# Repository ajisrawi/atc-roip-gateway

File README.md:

# ATC RoIP Gateway (VHF + HF, airborne)

Radio-over-IP gateway for aircraft ATC radios: bridges a VHF COM and an HF
transceiver to an IP network (Starlink aviation terminal) with an ED-137-style
RTP audio + PTT/COR stream.

```
Pilot/remote op ⇄ RTP over IP (Starlink) ⇄ [this gateway] ⇄ VHF COM + HF transceivers
```

## Deliverables

| Item | Where | Status |
|---|---|---|
| **Design document (PDF)** | `ATC-RoIP-Gateway-Design-Document.pdf` | 16 pages: study, diagrams, PCB, BOM, verification + schematic appendix |
| **Market study** | `docs/01-market-study.md` | sourced |
| **Design spec** | `docs/02-design-spec.md` | rev A |
| **Schematics** | `hardware/atc-roip-gateway/*.kicad_sch` | ERC 0 errors / 0 warnings, wired stubs + net labels |
| **PCB (4-layer, 125×95 mm)** | `hardware/atc-roip-gateway/atc-roip-gateway.kicad_pcb` | fully routed, 0 unconnected, 0 electrical DRC |
| **Fab outputs** | `hardware/atc-roip-gateway/fab/` | Gerber ZIP, drill, pick-and-place |
| **BOM** | `docs/BOM.csv` | 40 line items, 100 parts, MPNs assigned |
| **Firmware** | `firmware/` | ED-137-style stack (SIP + RTP/PTT/SQU + G.711), CMake, flash script |
| **Generators** | `tools/` | schematic/PCB/BOM/doc generation + checks (reproducible) |

## Hardware summary
| Block | Part |
|---|---|
| MCU | STM32H743VIT6 (Ethernet MAC + SAI, runs lwIP + RTP) |
| Ethernet | LAN8742A RMII PHY + magnetics-integrated RJ45 |
| Audio | TLV320AIC23B stereo codec — Left = VHF, Right = HF |
| Radio isolation | 600:600 Ω transformers (RX/TX ×2), PC817 optos (PTT + COR ×2) |
| Radio connector | DB25 (pinout in design spec §5.1) |
| Power | 28 V DC bus → LM2576HV-5.0 buck → AMS1117-3.3, split analog rail |

## Regenerating everything
```bash
python tools/design.py            # schematics
python tools/make_bom.py          # BOM from netlist
python tools/make_design_doc.py   # design document PDF
# PCB: tools/make_pcb.py (placement) + Freerouting + tools/power_fanout_final.py
```

## Status / caveats
- Rev A prototype: not TSO'd, no DO-160 qualification, no DO-178C artifacts.
- ED-137: hardware + firmware structured for the ED-137B Radio profile; exact
  extension bit-fields and SDP attributes must be verified against the
  licensed EUROCAE text + a conformance tool before claiming compliance.
- Transformer footprint (DIP-4) and DB25 gender are placeholders — confirm
  against the chosen audio transformer and aircraft harness.
- Firmware builds against STM32CubeH7 (user fetches; see `firmware/README.md`)
  and needs the four board-config files copied per `firmware/src/config/README.md`.

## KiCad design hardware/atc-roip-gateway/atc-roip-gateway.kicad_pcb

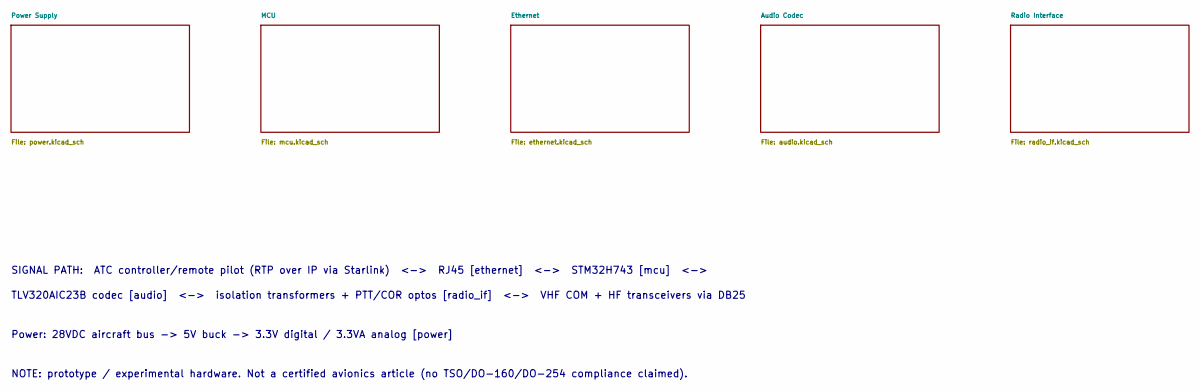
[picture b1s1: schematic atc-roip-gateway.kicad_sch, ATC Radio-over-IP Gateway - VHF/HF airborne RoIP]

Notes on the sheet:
SIGNAL PATH: ATC controller/remote pilot (RTP over IP via Starlink) <-> RJ45 [ethernet] <-> STM32H743 [mcu] <->
TLV320AIC23B codec [audio] <-> isolation transformers + PTT/COR optos [radio_if] <-> VHF COM + HF transceivers via DB25
Power: 28VDC aircraft bus -> 5V buck -> 3.3V digital / 3.3VA analog [power]
NOTE: prototype / experimental hardware. Not a certified avionics article (no TSO/DO-160/DO-254 compliance claimed).

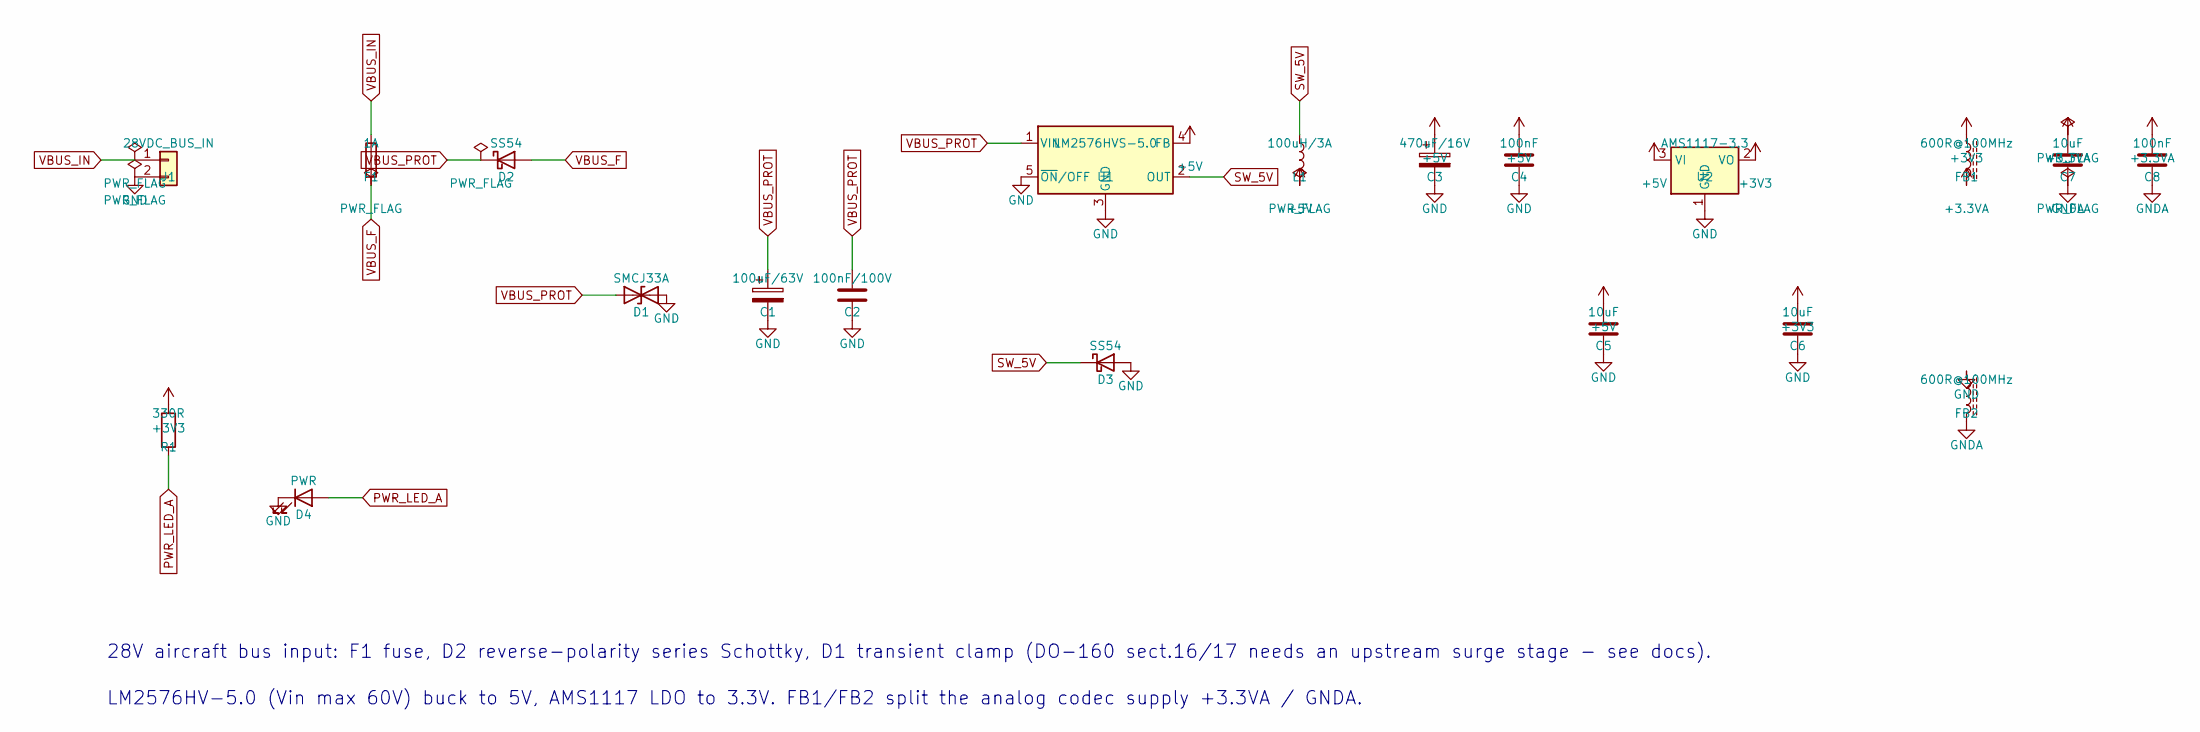
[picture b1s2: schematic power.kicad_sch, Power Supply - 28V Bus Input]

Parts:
C1: 100uF/63V; CP_Elec_8x10
C2: 100nF/100V; C_0805_2012Metric
C3: 470uF/16V; CP_Elec_8x10
C4, C8: 100nF; C_0603_1608Metric
C5, C6, C7: 10uF; C_0805_2012Metric
D1: SMCJ33A; D_SMC
D2, D3: SS54; D_SMA
D4: PWR; LED_0603_1608Metric
F1: 1A; Fuse_1206_3216Metric
FB1, FB2: 600R@100MHz; L_0805_2012Metric
J1: 28VDC_BUS_IN; TerminalBlock_Phoenix_MKDS-1,5-2_1x02_P5.00mm_Horizontal
L1: 100uH/3A; L_12x12mm_H8mm
R1: 330R; R_0603_1608Metric
U1: LM2576HVS-5.0; TO-263-5_TabPin3
U2: AMS1117-3.3; SOT-223-3_TabPin2

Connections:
+3V3: C6.1, FB1.1, R1.1, U2.2 (VO); also elsewhere on the board
PWR_LED_A: D4.2 (A), R1.2
SW_5V: D3.1 (K), L1.1, U1.2 (OUT)

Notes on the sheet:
28V aircraft bus input: F1 fuse, D2 reverse-polarity series Schottky, D1 transient clamp (DO-160 sect.16/17 needs an upstream surge stage - see docs).
LM2576HV-5.0 (Vin max 60V) buck to 5V, AMS1117 LDO to 3.3V. FB1/FB2 split the analog codec supply +3.3VA / GNDA.

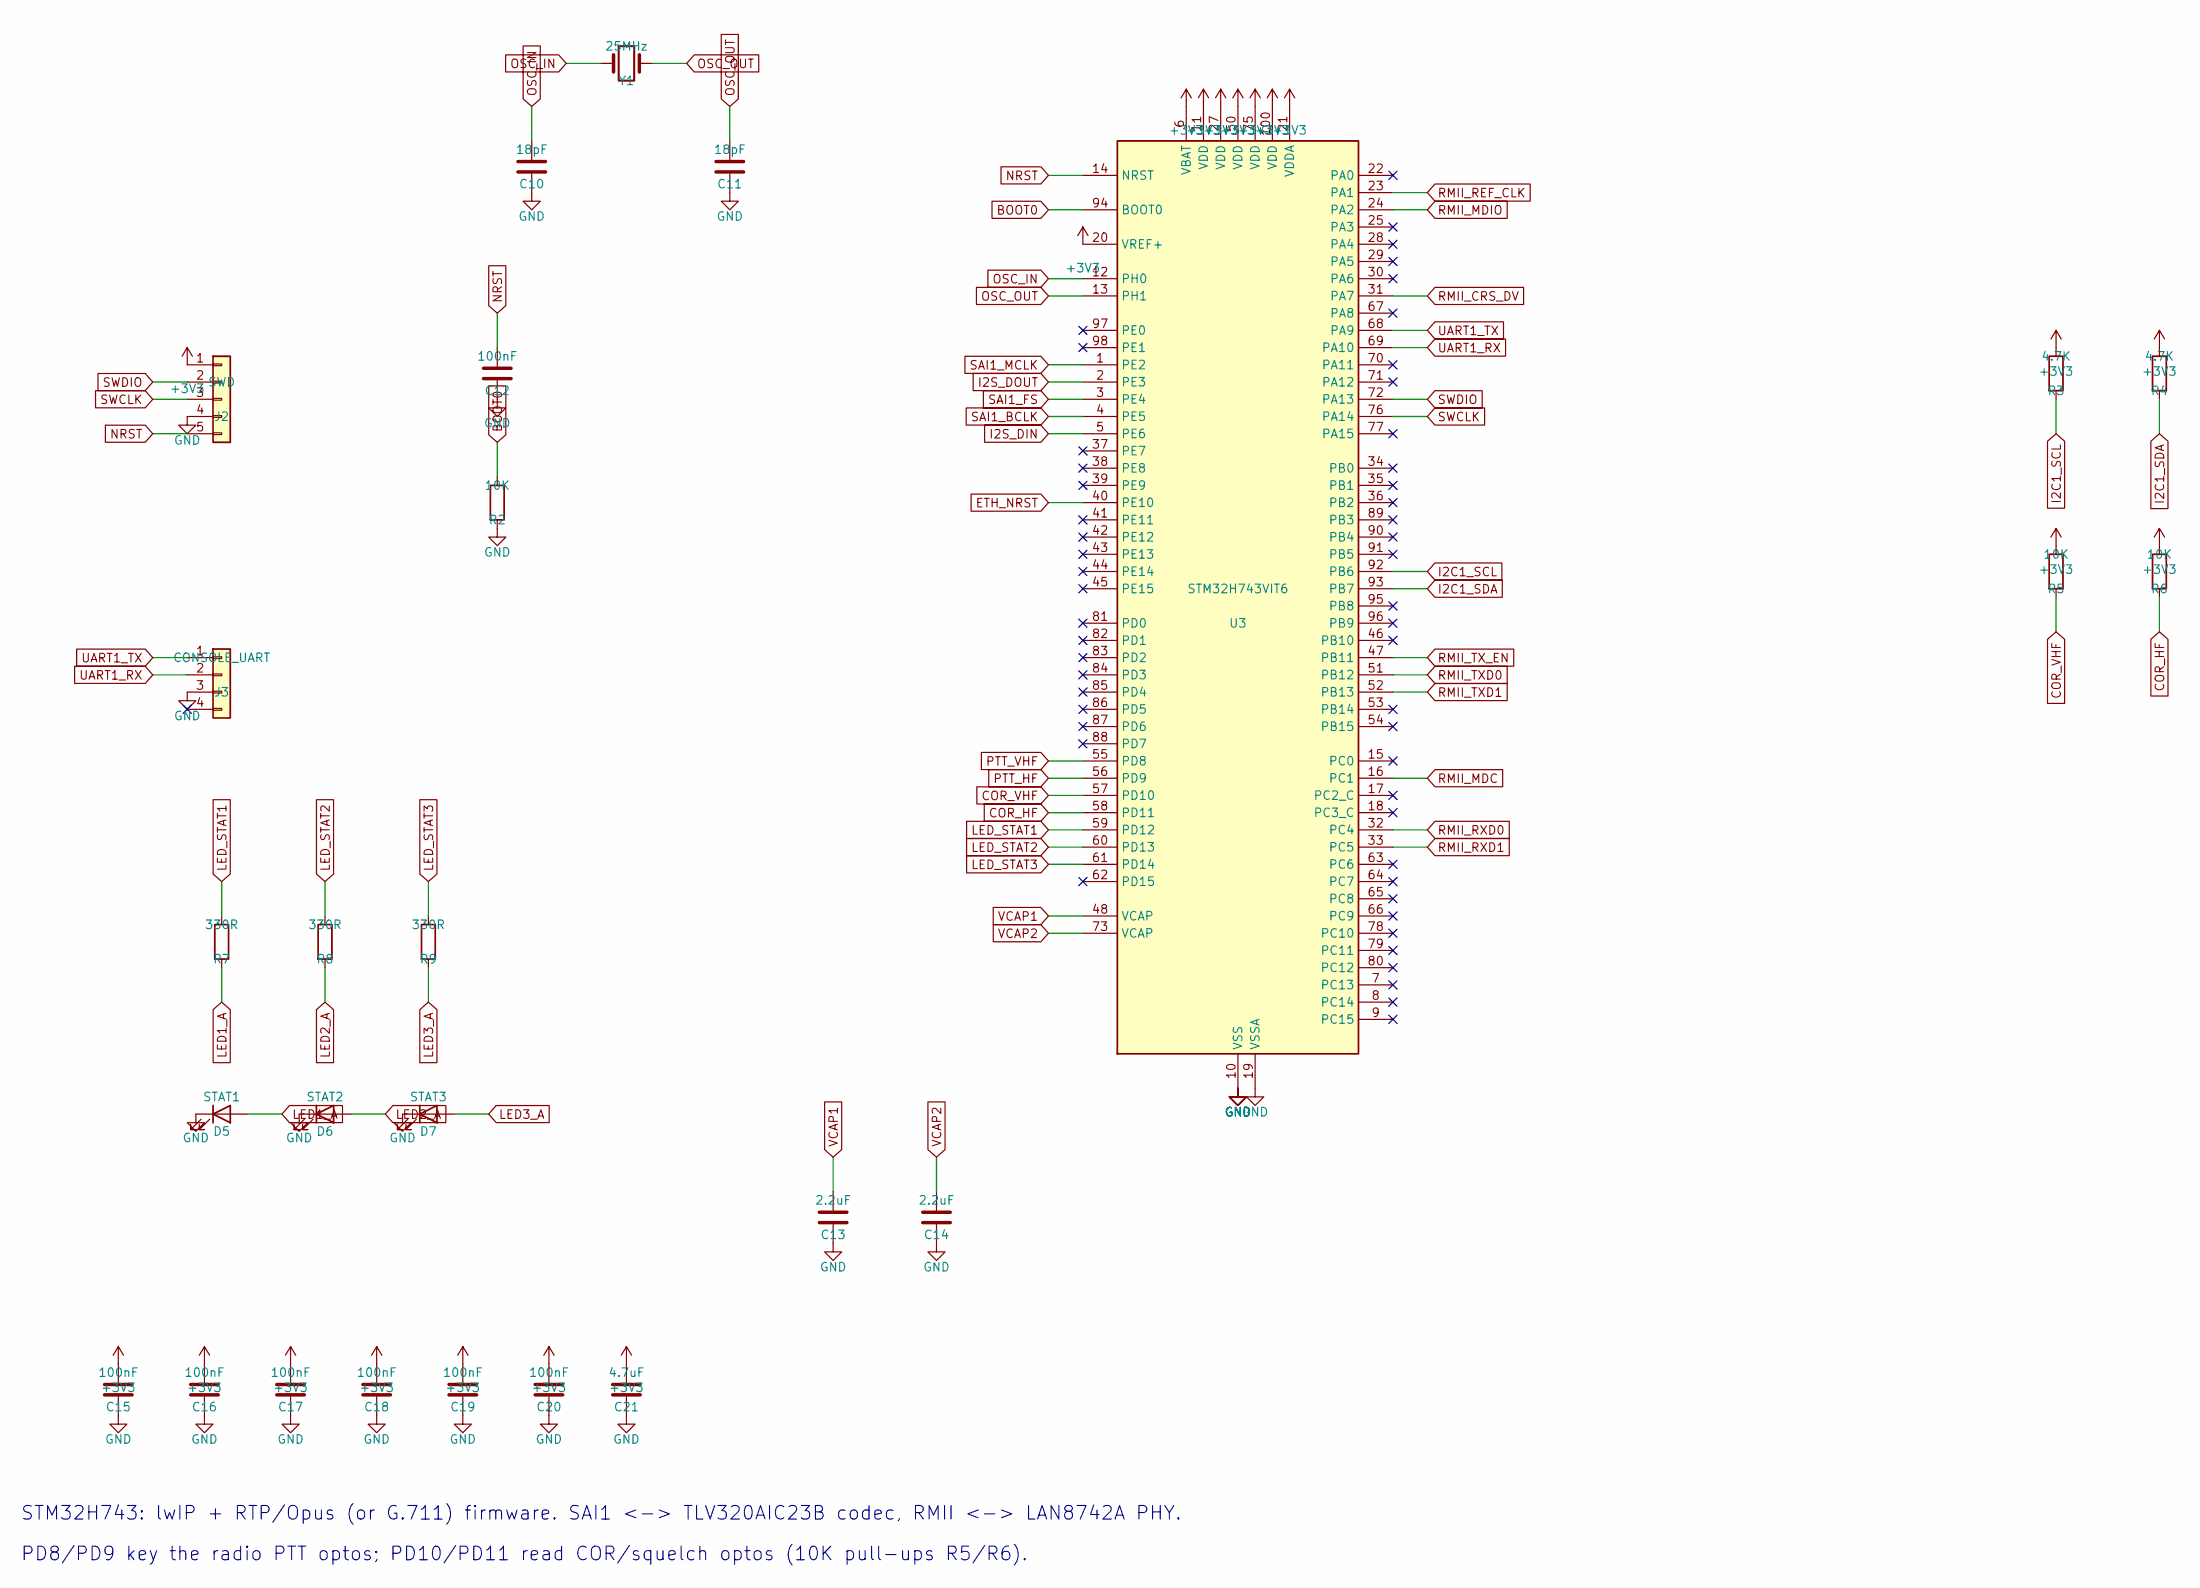
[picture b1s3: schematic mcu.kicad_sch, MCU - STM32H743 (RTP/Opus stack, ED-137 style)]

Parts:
C10, C11: 18pF; C_0603_1608Metric
C12, C15, C16, C17, C18, C19, C20: 100nF; C_0603_1608Metric
C13, C14: 2.2uF; C_0805_2012Metric
C21: 4.7uF; C_0805_2012Metric
D5: STAT1; LED_0603_1608Metric
D6: STAT2; LED_0603_1608Metric
D7: STAT3; LED_0603_1608Metric
J2: SWD; PinHeader_1x05_P2.54mm_Vertical
J3: CONSOLE_UART; PinHeader_1x04_P2.54mm_Vertical
R2, R5, R6: 10K; R_0603_1608Metric
R3, R4: 4.7K; R_0603_1608Metric
R7, R8, R9: 330R; R_0603_1608Metric
U3: STM32H743VIT6; LQFP-100_14x14mm_P0.5mm
Y1: 25MHz; Crystal_SMD_3225-4Pin_3.2x2.5mm

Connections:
+3V3: C15.1, C16.1, C17.1, C18.1, C19.1, C20.1, C21.1, J2.1, R3.1, R4.1, R5.1, R6.1, U3.6 (VBAT), U3.11 (VDD), U3.20 (VREF+), U3.21 (VDDA), U3.27 (VDD), U3.50 (VDD), U3.75 (VDD), U3.100 (VDD); also elsewhere on the board
BOOT0: R2.1, U3.94 (BOOT0)
COR_HF: R6.2, U3.58 (PD11); also elsewhere on the board
COR_VHF: R5.2, U3.57 (PD10); also elsewhere on the board
ETH_NRST: U3.40 (PE10); also elsewhere on the board
I2C1_SCL: R3.2, U3.92 (PB6); also elsewhere on the board
I2C1_SDA: R4.2, U3.93 (PB7); also elsewhere on the board
I2S_DIN: U3.5 (PE6); also elsewhere on the board
I2S_DOUT: U3.2 (PE3); also elsewhere on the board
LED1_A: D5.2 (A), R7.2
LED2_A: D6.2 (A), R8.2
LED3_A: D7.2 (A), R9.2
LED_STAT1: R7.1, U3.59 (PD12)
LED_STAT2: R8.1, U3.60 (PD13)
LED_STAT3: R9.1, U3.61 (PD14)
NRST: C12.1, J2.5, U3.14 (NRST)
OSC_IN: C10.1, U3.12 (PH0), Y1.1
OSC_OUT: C11.1, U3.13 (PH1), Y1.2
PTT_HF: U3.56 (PD9); also elsewhere on the board
PTT_VHF: U3.55 (PD8); also elsewhere on the board
RMII_CRS_DV: U3.31 (PA7); also elsewhere on the board
RMII_MDC: U3.16 (PC1); also elsewhere on the board
RMII_MDIO: U3.24 (PA2); also elsewhere on the board
RMII_REF_CLK: U3.23 (PA1); also elsewhere on the board
RMII_RXD0: U3.32 (PC4); also elsewhere on the board
RMII_RXD1: U3.33 (PC5); also elsewhere on the board
RMII_TXD0: U3.51 (PB12); also elsewhere on the board
RMII_TXD1: U3.52 (PB13); also elsewhere on the board
RMII_TX_EN: U3.47 (PB11); also elsewhere on the board
SAI1_BCLK: U3.4 (PE5); also elsewhere on the board
SAI1_FS: U3.3 (PE4); also elsewhere on the board
SAI1_MCLK: U3.1 (PE2); also elsewhere on the board
SWCLK: J2.3, U3.76 (PA14)
SWDIO: J2.2, U3.72 (PA13)
UART1_RX: J3.2, U3.69 (PA10)
UART1_TX: J3.1, U3.68 (PA9)
VCAP1: C13.1, U3.48 (VCAP)
VCAP2: C14.1, U3.73 (VCAP)

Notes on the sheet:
STM32H743: lwIP + RTP/Opus (or G.711) firmware. SAI1 <-> TLV320AIC23B codec, RMII <-> LAN8742A PHY.
PD8/PD9 key the radio PTT optos; PD10/PD11 read COR/squelch optos (10K pull-ups R5/R6).

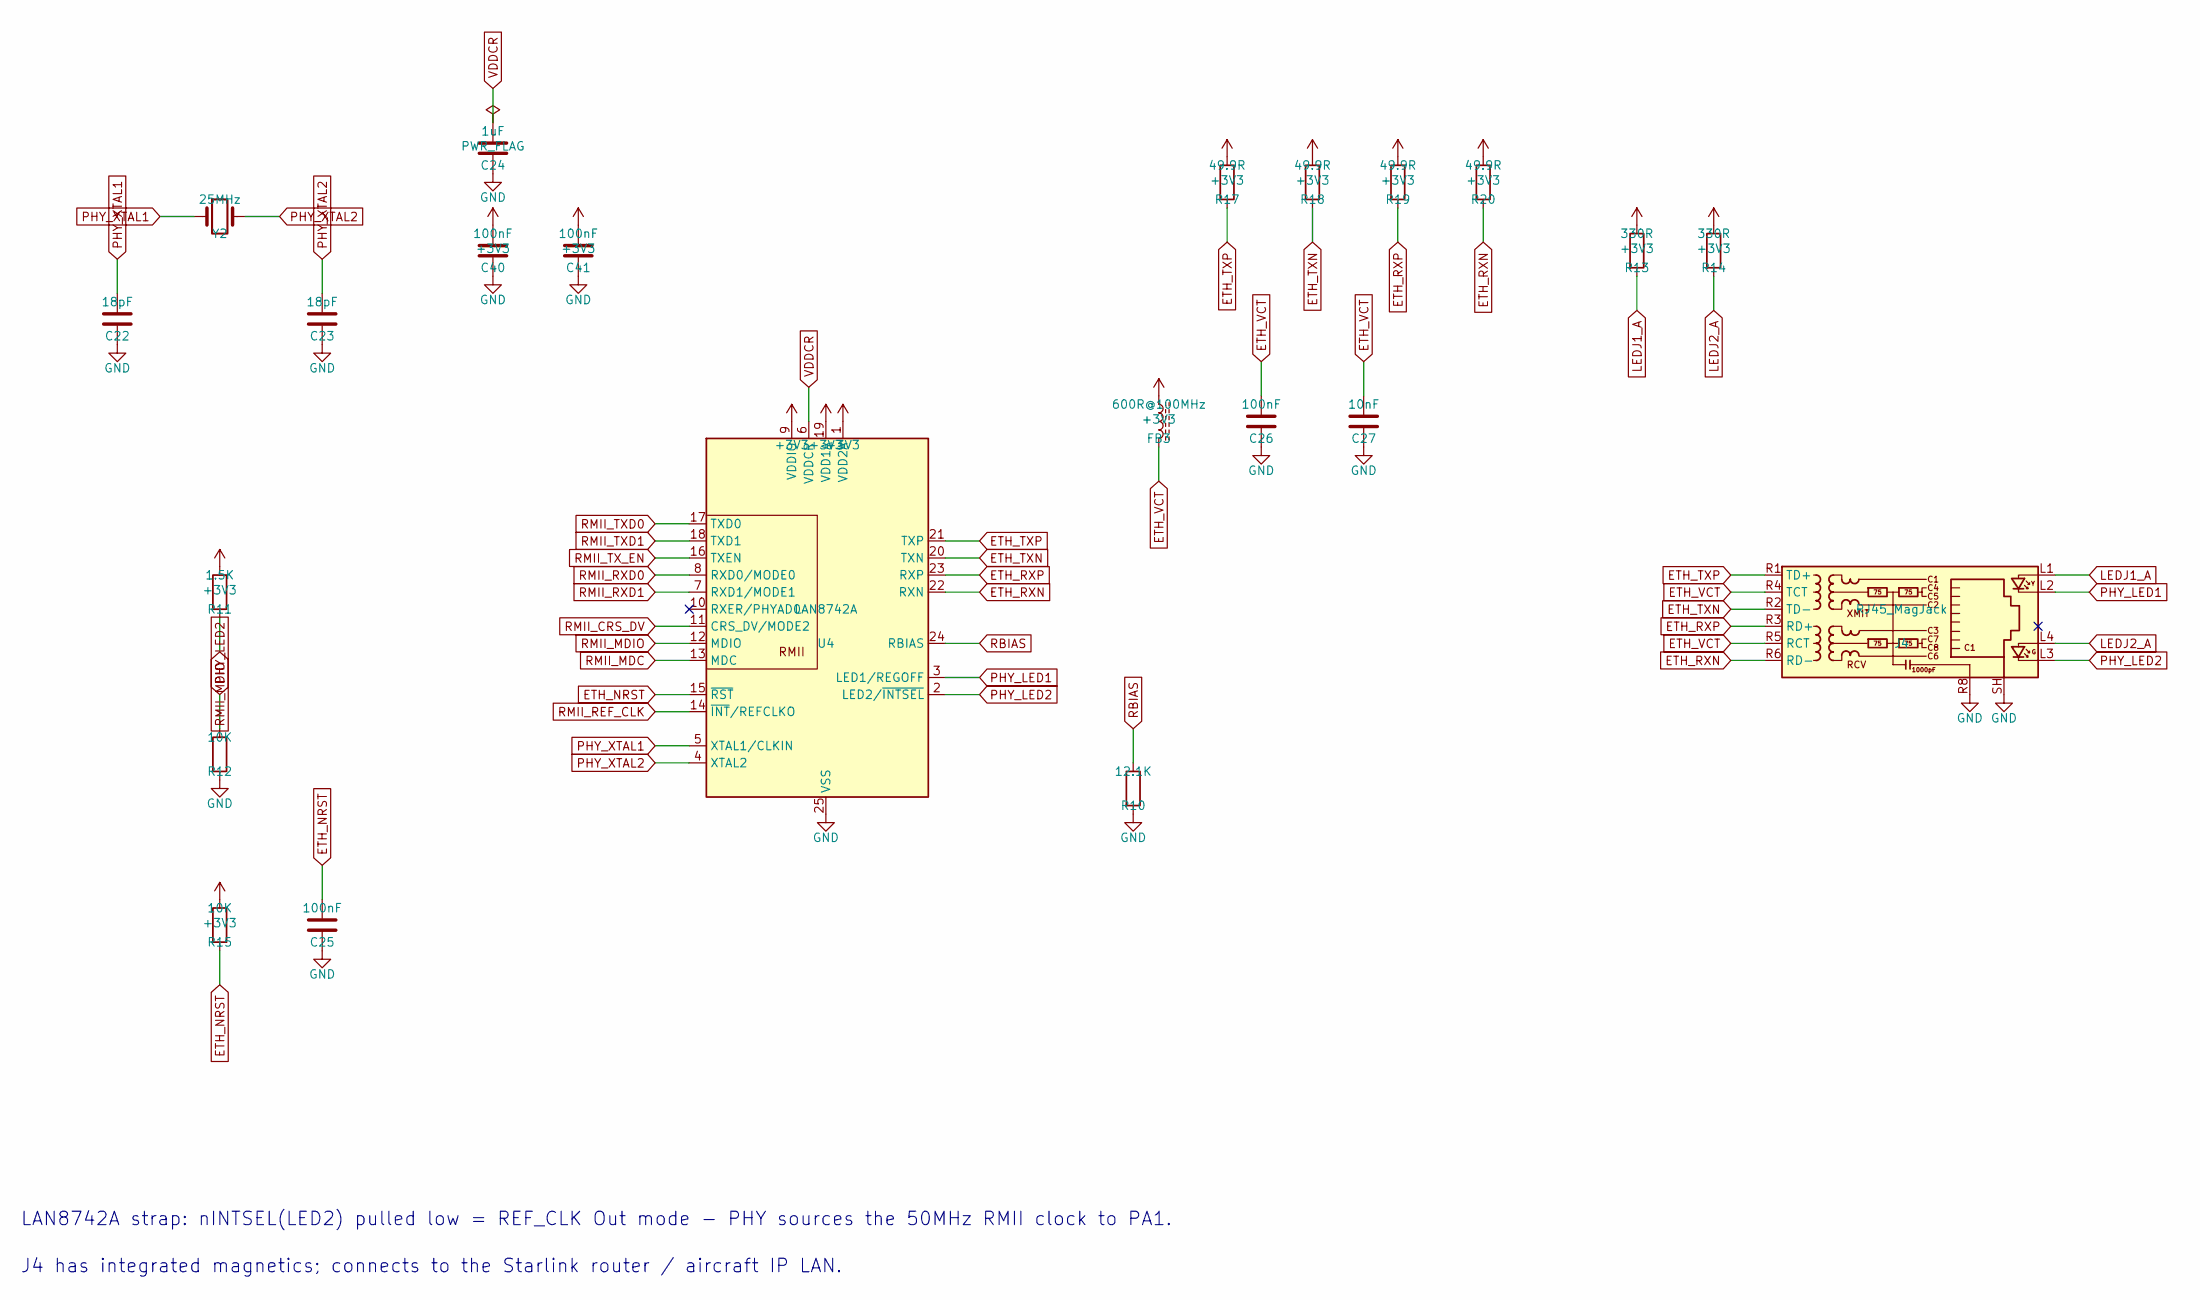
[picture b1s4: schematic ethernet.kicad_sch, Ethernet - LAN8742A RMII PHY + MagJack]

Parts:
C22, C23: 18pF; C_0603_1608Metric
C24: 1uF; C_0603_1608Metric
C25, C26, C40, C41: 100nF; C_0603_1608Metric
C27: 10nF; C_0603_1608Metric
FB3: 600R@100MHz; L_0805_2012Metric
J4: RJ45_MagJack; RJ45_Amphenol_RJMG1BD3B8K1ANR
R10: 12.1K; R_0603_1608Metric
R11: 1.5K; R_0603_1608Metric
R12, R15: 10K; R_0603_1608Metric
R13, R14: 330R; R_0603_1608Metric
R17, R18, R19, R20: 49.9R; R_0603_1608Metric
U4: LAN8742A; QFN-24-1EP_4x4mm_P0.5mm_EP2.6x2.6mm
Y2: 25MHz; Crystal_SMD_3225-4Pin_3.2x2.5mm

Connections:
+3V3: C40.1, C41.1, FB3.1, R11.1, R13.1, R14.1, R15.1, R17.1, R18.1, R19.1, R20.1, U4.1 (VDD2A), U4.9 (VDDIO), U4.19 (VDD1A); also elsewhere on the board
ETH_NRST: C25.1, R15.2, U4.15 (~RST); also elsewhere on the board
ETH_RXN: J4.R6 (RD-), R20.2, U4.22 (RXN)
ETH_RXP: J4.R3 (RD+), R19.2, U4.23 (RXP)
ETH_TXN: J4.R2 (TD-), R18.2, U4.20 (TXN)
ETH_TXP: J4.R1 (TD+), R17.2, U4.21 (TXP)
ETH_VCT: C26.1, C27.1, FB3.2, J4.R4 (TCT), J4.R5 (RCT)
LEDJ1_A: J4.L1, R13.2
LEDJ2_A: J4.L4, R14.2
PHY_LED1: J4.L2, U4.3 (LED1/REGOFF)
PHY_LED2: J4.L3, R12.1, U4.2 (LED2/~INTSEL)
PHY_XTAL1: C22.1, U4.5 (XTAL1/CLKIN), Y2.1
PHY_XTAL2: C23.1, U4.4 (XTAL2), Y2.2
RBIAS: R10.1, U4.24 (RBIAS)
RMII_CRS_DV: U4.11 (CRS_DV/MODE2); also elsewhere on the board
RMII_MDC: U4.13 (MDC); also elsewhere on the board
RMII_MDIO: R11.2, U4.12 (MDIO); also elsewhere on the board
RMII_REF_CLK: U4.14 (~INT/REFCLKO); also elsewhere on the board
RMII_RXD0: U4.8 (RXD0/MODE0); also elsewhere on the board
RMII_RXD1: U4.7 (RXD1/MODE1); also elsewhere on the board
RMII_TXD0: U4.17 (TXD0); also elsewhere on the board
RMII_TXD1: U4.18 (TXD1); also elsewhere on the board
RMII_TX_EN: U4.16 (TXEN); also elsewhere on the board
VDDCR: C24.1, U4.6 (VDDCR)

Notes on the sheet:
LAN8742A strap: nINTSEL(LED2) pulled low = REF_CLK Out mode - PHY sources the 50MHz RMII clock to PA1.
J4 has integrated magnetics; connects to the Starlink router / aircraft IP LAN.

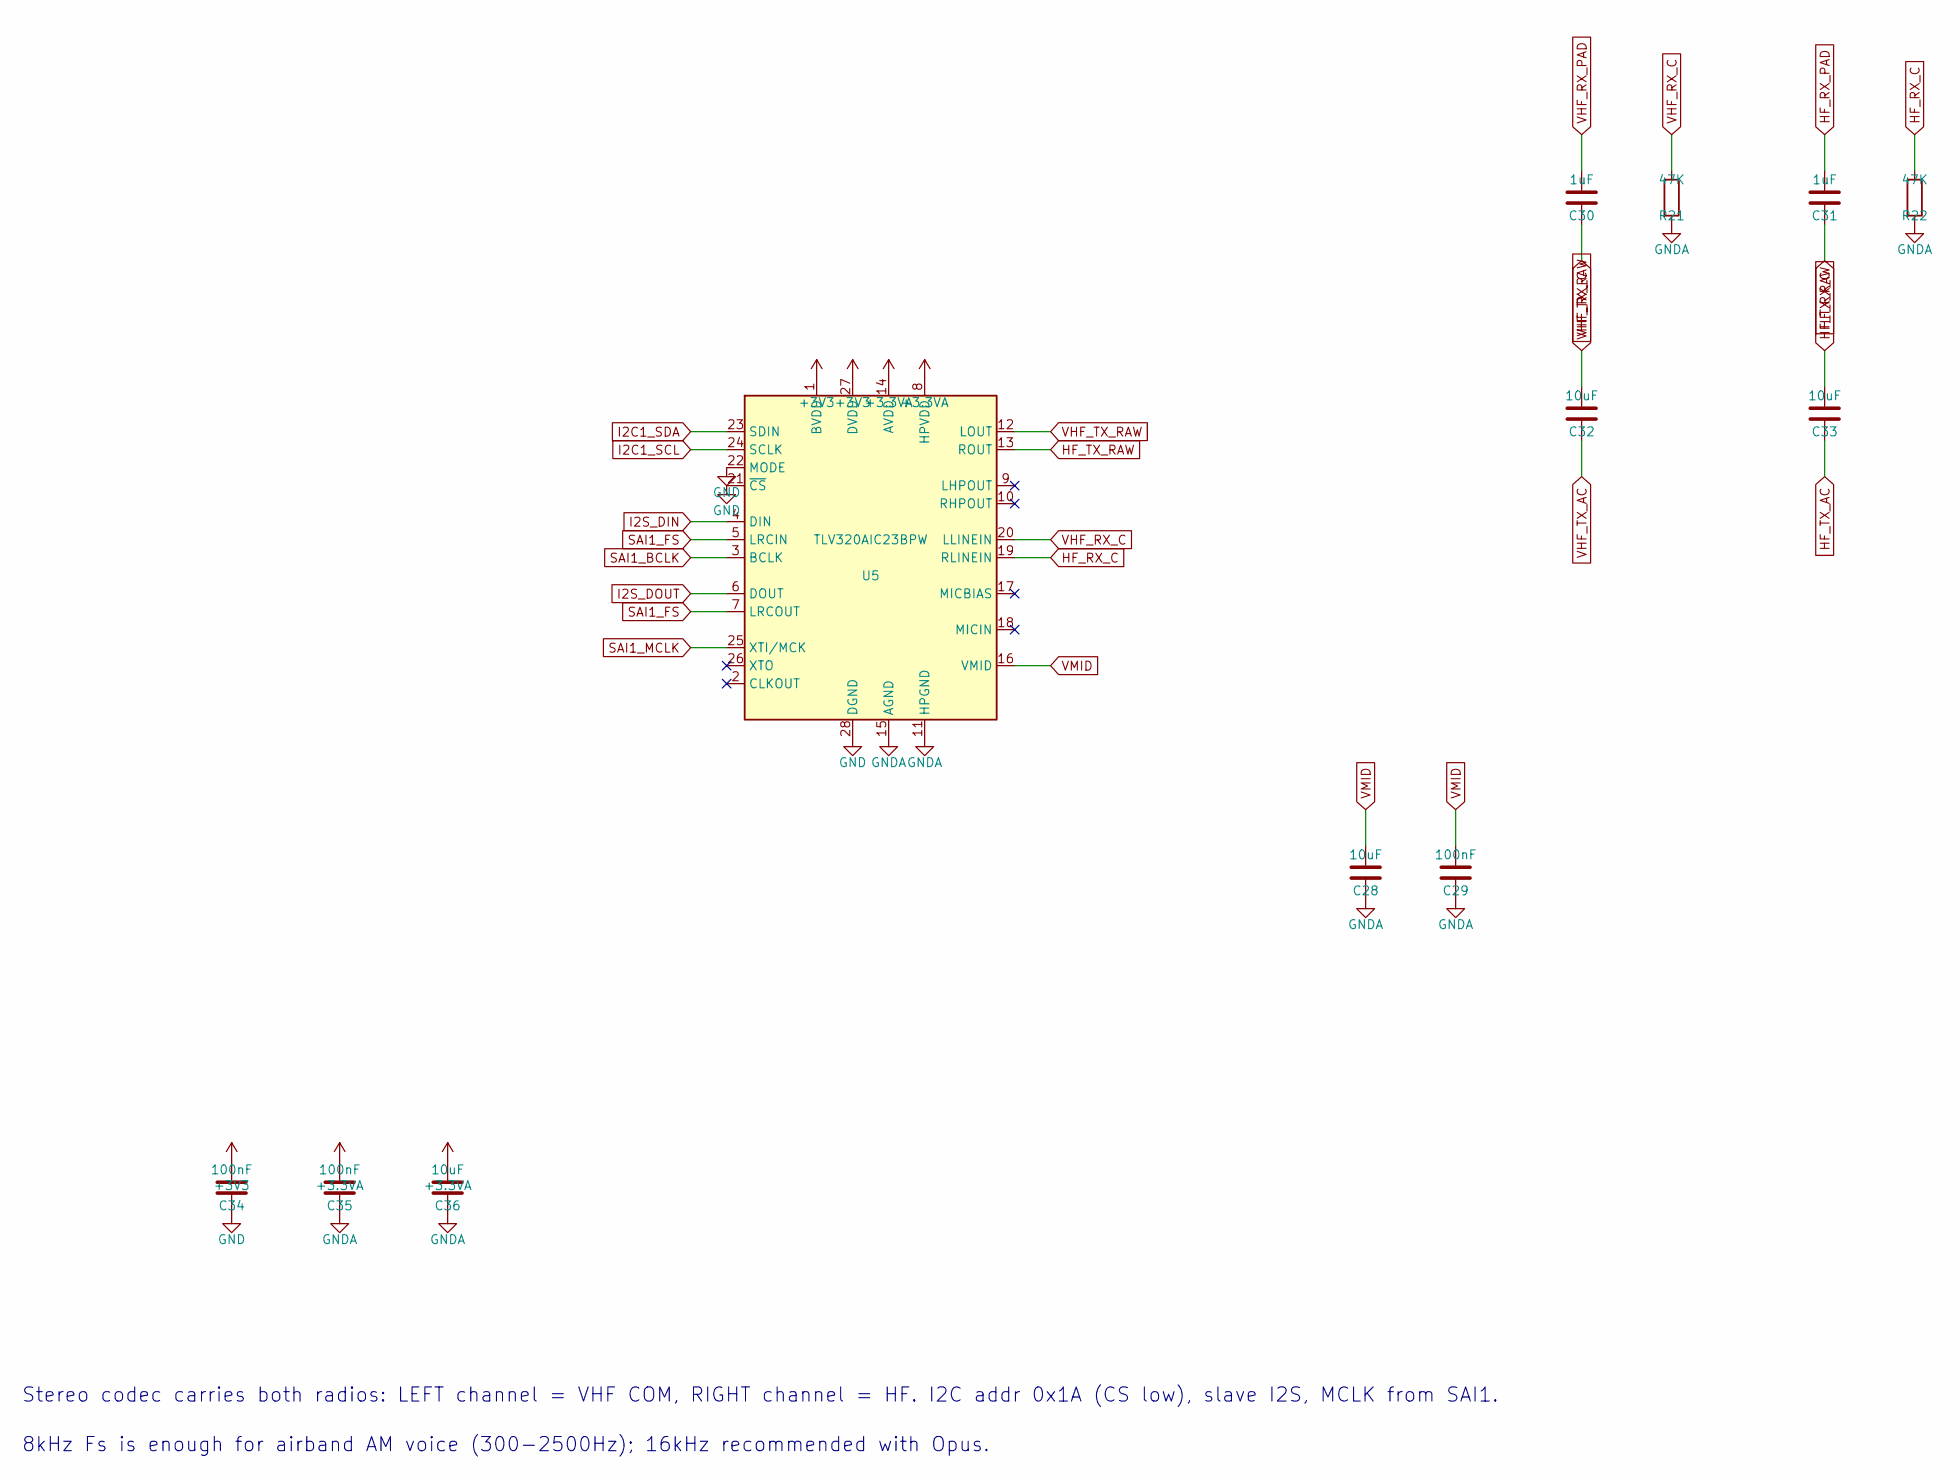
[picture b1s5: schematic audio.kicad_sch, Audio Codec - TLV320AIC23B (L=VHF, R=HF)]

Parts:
C28, C32, C33, C36: 10uF; C_0805_2012Metric
C29, C34, C35: 100nF; C_0603_1608Metric
C30, C31: 1uF; C_0603_1608Metric
R21, R22: 47K; R_0603_1608Metric
U5: TLV320AIC23BPW; TSSOP-28_4.4x9.7mm_P0.65mm

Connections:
+3V3: C34.1, U5.1 (BVDD), U5.27 (DVDD); also elsewhere on the board
HF_RX_C: C31.2, R22.1, U5.19 (RLINEIN)
HF_RX_PAD: C31.1; also elsewhere on the board
HF_TX_AC: C33.2; also elsewhere on the board
HF_TX_RAW: C33.1, U5.13 (ROUT)
I2C1_SCL: U5.24 (SCLK); also elsewhere on the board
I2C1_SDA: U5.23 (SDIN); also elsewhere on the board
I2S_DIN: U5.4 (DIN); also elsewhere on the board
I2S_DOUT: U5.6 (DOUT); also elsewhere on the board
SAI1_BCLK: U5.3 (BCLK); also elsewhere on the board
SAI1_FS: U5.5 (LRCIN), U5.7 (LRCOUT); also elsewhere on the board
SAI1_MCLK: U5.25 (XTI/MCK); also elsewhere on the board
VHF_RX_C: C30.2, R21.1, U5.20 (LLINEIN)
VHF_RX_PAD: C30.1; also elsewhere on the board
VHF_TX_AC: C32.2; also elsewhere on the board
VHF_TX_RAW: C32.1, U5.12 (LOUT)
VMID: C28.1, C29.1, U5.16 (VMID)

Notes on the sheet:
Stereo codec carries both radios: LEFT channel = VHF COM, RIGHT channel = HF. I2C addr 0x1A (CS low), slave I2S, MCLK from SAI1.
8kHz Fs is enough for airband AM voice (300-2500Hz); 16kHz recommended with Opus.

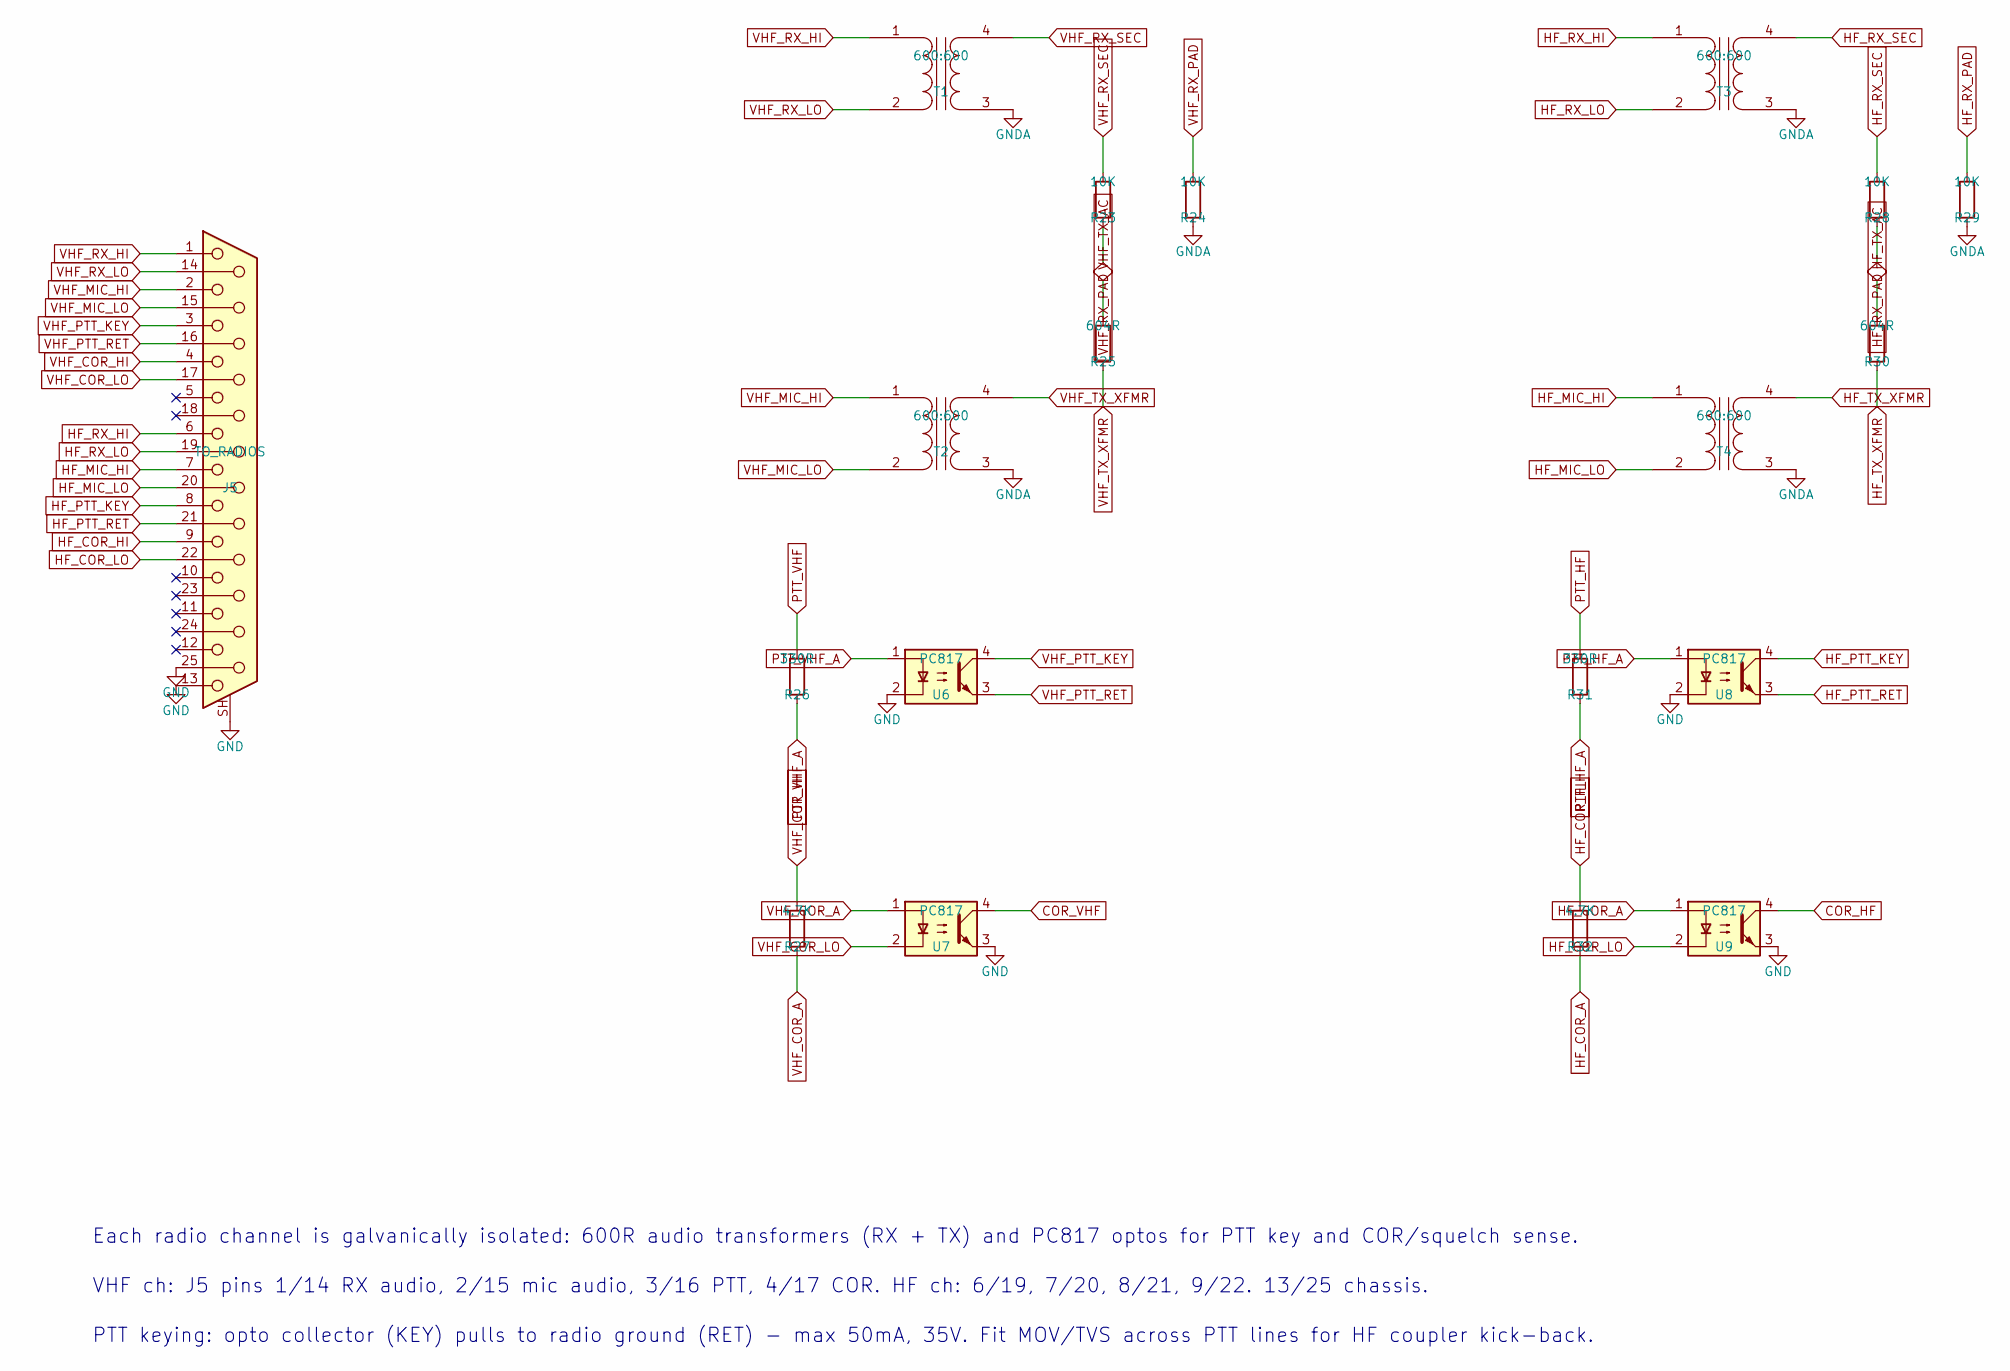
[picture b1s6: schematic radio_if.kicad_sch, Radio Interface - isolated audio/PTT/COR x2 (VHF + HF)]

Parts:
J5: TO_RADIOS; DSUB-25_Pins_Horizontal_P2.77x2.84mm_EdgePinOffset7.70mm_Ho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
R23, R24, R28, R29: 10K; R_0603_1608Metric
R25, R30: 604R; R_0603_1608Metric
R26, R31: 330R; R_0603_1608Metric
R27, R32: 4.7K; R_0603_1608Metric
T1, T2, T3, T4: 600:600; DIP-4_W10.16mm
U6, U7, U8, U9: PC817; DIP-4_W7.62mm

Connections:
COR_HF: U9.4; also elsewhere on the board
COR_VHF: U7.4; also elsewhere on the board
HF_COR_A: R32.2, U9.1
HF_COR_HI: J5.9, R32.1
HF_COR_LO: J5.22, U9.2
HF_MIC_HI: J5.7, T4.1 (AA)
HF_MIC_LO: J5.20, T4.2 (AB)
HF_PTT_KEY: J5.8, U8.4
HF_PTT_RET: J5.21, U8.3
HF_RX_HI: J5.6, T3.1 (AA)
HF_RX_LO: J5.19, T3.2 (AB)
HF_RX_PAD: R28.2, R29.1; also elsewhere on the board
HF_RX_SEC: R28.1, T3.4 (SB)
HF_TX_AC: R30.1; also elsewhere on the board
HF_TX_XFMR: R30.2, T4.4 (SB)
PTT_HF: R31.1; also elsewhere on the board
PTT_HF_A: R31.2, U8.1
PTT_VHF: R26.1; also elsewhere on the board
PTT_VHF_A: R26.2, U6.1
VHF_COR_A: R27.2, U7.1
VHF_COR_HI: J5.4, R27.1
VHF_COR_LO: J5.17, U7.2
VHF_MIC_HI: J5.2, T2.1 (AA)
VHF_MIC_LO: J5.15, T2.2 (AB)
VHF_PTT_KEY: J5.3, U6.4
VHF_PTT_RET: J5.16, U6.3
VHF_RX_HI: J5.1, T1.1 (AA)
VHF_RX_LO: J5.14, T1.2 (AB)
VHF_RX_PAD: R23.2, R24.1; also elsewhere on the board
VHF_RX_SEC: R23.1, T1.4 (SB)
VHF_TX_AC: R25.1; also elsewhere on the board
VHF_TX_XFMR: R25.2, T2.4 (SB)

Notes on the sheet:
Each radio channel is galvanically isolated: 600R audio transformers (RX + TX) and PC817 optos for PTT key and COR/squelch sense.
VHF ch: J5 pins 1/14 RX audio, 2/15 mic audio, 3/16 PTT, 4/17 COR. HF ch: 6/19, 7/20, 8/21, 9/22. 13/25 chassis.
PTT keying: opto collector (KEY) pulls to radio ground (RET) - max 50mA, 35V. Fit MOV/TVS across PTT lines for HF coupler kick-back.

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
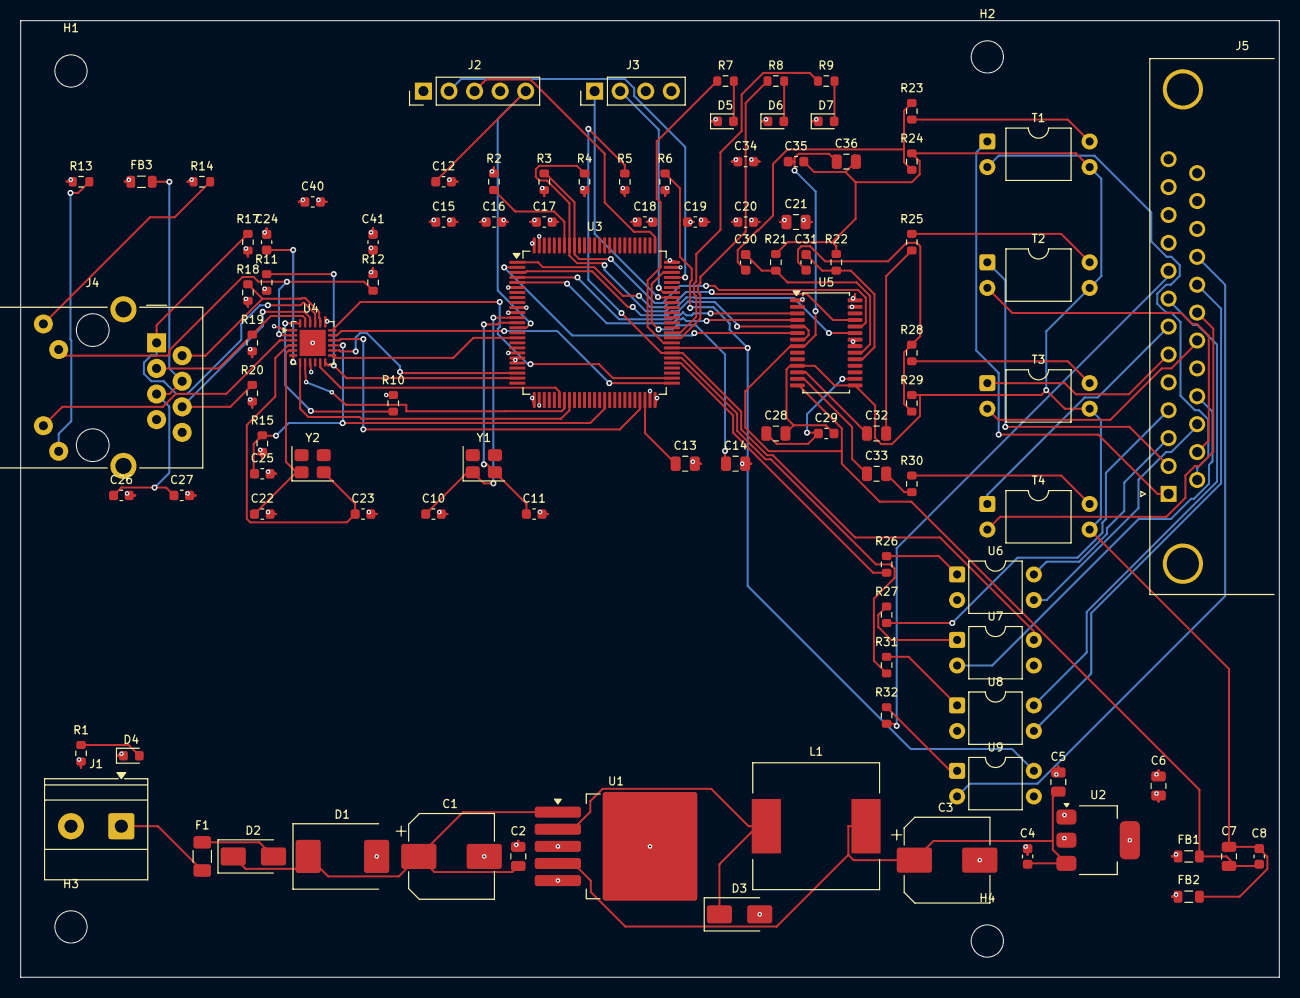
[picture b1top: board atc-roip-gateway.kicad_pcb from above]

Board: 4 copper layers, 125.0 x 95.0 mm, 104 parts (0 on the bottom side), 93 nets.

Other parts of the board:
H1, H2, H3, H4: M3; MountingHole_3.2mm_M3

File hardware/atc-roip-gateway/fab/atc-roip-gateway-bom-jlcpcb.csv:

Comment,Designator,Footprint,LCSC Part #,Manufacturer,MPN
100uF/63V,C1,CP_Elec_8x10,,Panasonic,EEE-FK1J101P
100nF/100V,C2,C_0805_2012Metric,,Samsung,CL21 series
470uF/16V,C3,CP_Elec_8x10,,Panasonic,EEE-FK1C471P
100nF,"C4,C8,C12,C15,C16,C17,C18,C19,C20,C25,C26,C29,C34,C35,C40,C41",C_0603_1608Metric,,Samsung,CL10 series
10uF,"C5,C6,C7,C28,C32,C33,C36",C_0805_2012Metric,,Samsung,CL21 series
18pF,"C10,C11,C22,C23",C_0603_1608Metric,,Samsung,CL10 series
2.2uF,"C13,C14",C_0805_2012Metric,,Samsung,CL21 series
4.7uF,C21,C_0805_2012Metric,,Samsung,CL21 series
1uF,"C24,C30,C31",C_0603_1608Metric,,Samsung,CL10 series
10nF,C27,C_0603_1608Metric,,Samsung,CL10 series
SMCJ33A,D1,D_SMC,,Littelfuse,SMCJ33A
SS54,"D2,D3",D_SMA,,Vishay / MDD,SS54
PWR,D4,LED_0603_1608Metric,,Everlight,19-217/GHC-YR1S2/3T
STAT1,D5,LED_0603_1608Metric,,Everlight,19-217/GHC-YR1S2/3T
STAT2,D6,LED_0603_1608Metric,,Everlight,19-217/GHC-YR1S2/3T
STAT3,D7,LED_0603_1608Metric,,Everlight,19-217/GHC-YR1S2/3T
1A,F1,Fuse_1206_3216Metric,,Littelfuse,0451001.MRL
600R@100MHz,"FB1,FB2,FB3",L_0805_2012Metric,,Murata,BLM21PG600SN1D
28VDC_BUS_IN,J1,"TerminalBlock_Phoenix_MKDS-1,5-2_1x02_P5.00mm_Horizontal",,Phoenix Contact,"1715022 (MKDS 1,5/2-5,08)"
SWD,J2,PinHeader_1x05_P2.54mm_Vertical,,generic,PinHeader 1x05 2.54mm
CONSOLE_UART,J3,PinHeader_1x04_P2.54mm_Vertical,,generic,PinHeader 1x04 2.54mm
RJ45_MagJack,J4,RJ45_Amphenol_RJMG1BD3B8K1ANR,,Amphenol,RJMG1BD3B8K1ANR
TO_RADIOS,J5,DSUB-25_Pins_Horizontal_P2.77x2.84mm_EdgePinOffset7.70mm_Housed_MountingHolesOffset9.12mm,,NorComp / Amphenol,182-025-113R531 (female) or L717SDB25P
100uH/3A,L1,L_12x12mm_H8mm,,Bourns,SRP1265A-101M
330R,"R1,R7,R8,R9,R13,R14,R26,R31",R_0603_1608Metric,,Yageo,RC0603FR-07330RL
10K,"R2,R5,R6,R12,R15,R23,R24,R28,R29",R_0603_1608Metric,,Yageo,RC0603FR-0710KL
4.7K,"R3,R4,R27,R32",R_0603_1608Metric,,Yageo,RC0603FR-074.7KL
12.1K,R10,R_0603_1608Metric,,Yageo,RC0603FR-0712.1KL
1.5K,R11,R_0603_1608Metric,,Yageo,RC0603FR-071.5KL
49.9R,"R17,R18,R19,R20",R_0603_1608Metric,,Yageo,RC0603FR-0749.9RL
47K,"R21,R22",R_0603_1608Metric,,Yageo,RC0603FR-0747KL
604R,"R25,R30",R_0603_1608Metric,,Yageo,RC0603FR-07604RL
600:600,"T1,T2,T3,T4",DIP-4_W10.16mm,,Triad Magnetics,SP-66 (or Tamura TTC-108)
LM2576HVS-5.0,U1,TO-263-5_TabPin3,,Texas Instruments,LM2576HVS-5.0/NOPB
AMS1117-3.3,U2,SOT-223-3_TabPin2,,AMS / UMW,AMS1117-3.3
STM32H743VIT6,U3,LQFP-100_14x14mm_P0.5mm,,STMicroelectronics,STM32H743VIT6
LAN8742A,U4,QFN-24-1EP_4x4mm_P0.5mm_EP2.6x2.6mm,,Microchip,LAN8742A-CZ-TR
TLV320AIC23BPW,U5,TSSOP-28_4.4x9.7mm_P0.65mm,,Texas Instruments,TLV320AIC23BPWR
PC817,"U6,U7,U8,U9",DIP-4_W7.62mm,,Sharp,PC817X2NSZ9F
25MHz,"Y1,Y2",Crystal_SMD_3225-4Pin_3.2x2.5mm,,Abracon,ABM3-25.000MHZ-D2Y-T
